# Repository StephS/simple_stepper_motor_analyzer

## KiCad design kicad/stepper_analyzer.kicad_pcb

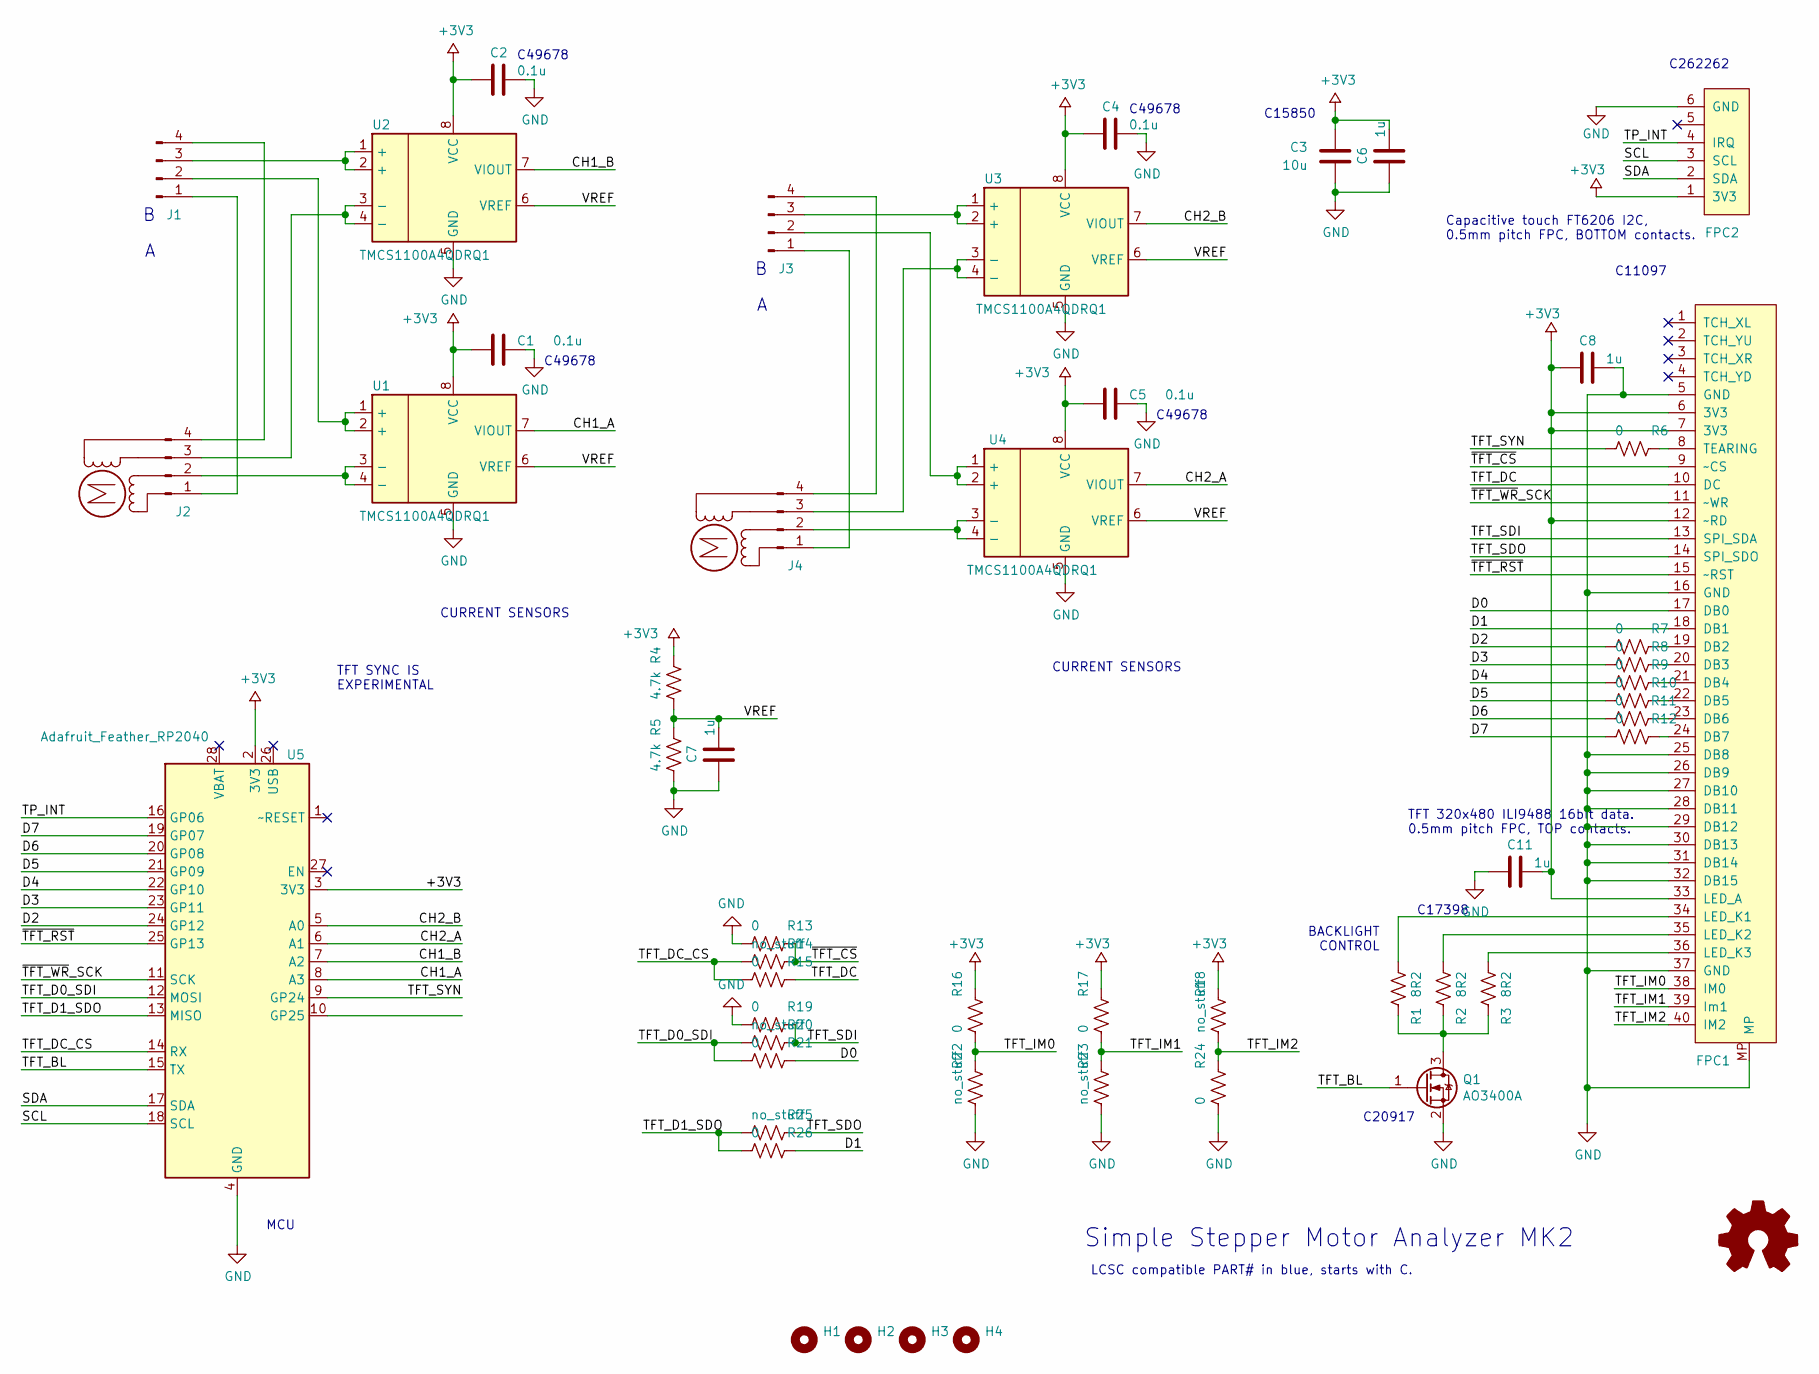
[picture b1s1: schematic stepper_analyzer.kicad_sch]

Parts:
C1, C2, C4, C5: 0.1u; C_0805_2012Metric_Pad1.15x1.40mm_HandSolder; LCSC C49678
C3: 10u; C_0805_2012Metric_Pad1.15x1.40mm_HandSolder; LCSC C15850
C6, C7, C8, C11: 1u; C_0805_2012Metric_Pad1.15x1.40mm_HandSolder
FPC1: Connector_Conn_01x40_Female; JUSHUO-AFC07-S40ECC-00_40P_05mm_flipped; LCSC C11097
FPC2: FPC connector, 6 pins, 0.5mm, BOTTOM contacts; JUSHUO-AFC01-S06FCC-00_6p_05mm; LCSC C262262
H1, H2, H3, H4: MountingHole; MountingHole_2.5mm_Pad_Via
J1, J2, J3, J4: Connector_Conn_01x04_Male; connector_4pins_horizontal
LOGO1: Logo_Open_Hardware_Small; OSHW-Logo2_9.8x8mm_SilkScreen
M1, M2: Motor; null_footprint
Q1: AO3400A; SOT-23; LCSC C20917
R1, R2, R3: 8R2; R_0805_2012Metric_Pad1.15x1.40mm_HandSolder; LCSC C25330
R4, R5: 4.7k; R_0402_1005Metric_Pad0.72x0.64mm_HandSolder
R6, R7, R8, R9, R10, R11, R12, R13, R15, R16, R17, R19, R21, R24, R26: 0; R_0402_1005Metric_Pad0.72x0.64mm_HandSolder
R14, R18, R20, R22, R23, R25: no_stuff; R_0402_1005Metric_Pad0.72x0.64mm_HandSolder
U1, U2, U3, U4: TMCS1100A4QDRQ1; SOIC-8_3.9x4.9mm_P1.27mm
U5: Adafruit_Feather_RP2040; Adafruit_Feather

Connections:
+3V3: C1.2, C2.2, C3.2, C4.2, C5.2, C6.1, C8.2, C11.1, FPC1.6 (3V3), FPC1.7 (3V3), FPC1.12 (~RD), FPC1.33 (LED_A), FPC2.1 (3V3), R4.1, R16.1, R17.1, R18.1, U1.8 (VCC), U2.8 (VCC), U3.8 (VCC), U4.8 (VCC), U5.2 (3V3), U5.3 (3V3)
/CH1_A: U1.7 (VIOUT), U5.8 (A3)
/CH1_B: U2.7 (VIOUT), U5.7 (A2)
/CH2_A: U4.7 (VIOUT), U5.6 (A1)
/CH2_B: U3.7 (VIOUT), U5.5 (A0)
/D0: FPC1.17 (DB0), R21.1
/D1: FPC1.18 (DB1), R26.1
/D2: R7.2, U5.24 (GP12)
/D3: R8.2, U5.23 (GP11)
/D4: R9.2, U5.22 (GP10)
/D5: R10.2, U5.21 (GP09)
/D6: R11.2, U5.20 (GP08)
/D7: R12.2, U5.19 (GP07)
/SCL: FPC2.3 (SCL), U5.18 (SCL)
/SDA: FPC2.2 (SDA), U5.17 (SDA)
/TFT_BL: Q1.1 (G), U5.15 (TX)
/TFT_D0_SDI: R20.2, R21.2, U5.12 (MOSI)
/TFT_D1_SDO: R25.2, R26.2, U5.13 (MISO)
/TFT_DC: FPC1.10 (DC), R15.1
/TFT_DC_CS: R14.2, R15.2, U5.14 (RX)
/TFT_IM0: FPC1.38 (IM0), R16.2, R22.1
/TFT_IM1: FPC1.39 (Im1), R17.2, R23.1
/TFT_IM2: FPC1.40 (IM2), R18.2, R24.1
/TFT_SDI: FPC1.13 (SPI_SDA), R19.1, R20.1
/TFT_SDO: FPC1.14 (SPI_SDO), R25.1
/TFT_SYN: R6.2, U5.9 (GP24)
/TP_INT: FPC2.4 (IRQ), U5.16 (GP06)
/VREF: C7.1, R4.2, R5.1, U1.6 (VREF), U2.6 (VREF), U3.6 (VREF), U4.6 (VREF)
/~TFT_CS: FPC1.9 (~CS), R13.1, R14.1
/~TFT_RST: FPC1.15 (~RST), U5.25 (GP13)
/~TFT_WR_SCK: FPC1.11 (~WR), U5.11 (SCK)
GND: C1.1, C2.1, C3.1, C4.1, C5.1, C6.2, C7.2, C8.1, C11.2, FPC1.5 (GND), FPC1.16 (GND), FPC1.25 (DB8), FPC1.26 (DB9), FPC1.27 (DB10), FPC1.28 (DB11), FPC1.29 (DB12), FPC1.30 (DB13), FPC1.31 (DB14), FPC1.32 (DB15), FPC1.37 (GND), FPC1.MP, FPC2.6 (GND), Q1.2 (S), R5.2, R13.2, R19.2, R22.2, R23.2, R24.2, U1.5 (GND), U2.5 (GND), U3.5 (GND), U4.5 (GND), U5.4 (GND)
unnamed: FPC1.8 (TEARING), R6.1
unnamed: FPC1.19 (DB2), R7.1
unnamed: FPC1.20 (DB3), R8.1
unnamed: FPC1.21 (DB4), R9.1
unnamed: FPC1.22 (DB5), R10.1
unnamed: FPC1.23 (DB6), R11.1
unnamed: FPC1.24 (DB7), R12.1
unnamed: FPC1.34 (LED_K1), R1.2
unnamed: FPC1.35 (LED_K2), R2.2
unnamed: FPC1.36 (LED_K3), R3.2
unnamed: J1.1, J2.1
unnamed: J1.2, U1.1 (+), U1.2 (+)
unnamed: J1.3, U2.1 (+), U2.2 (+)
unnamed: J1.4, J2.4
unnamed: J2.2, U1.3 (-), U1.4 (-)
unnamed: J2.3, U2.3 (-), U2.4 (-)
unnamed: J3.1, J4.1
unnamed: J3.2, U4.1 (+), U4.2 (+)
unnamed: J3.3, U3.1 (+), U3.2 (+)
unnamed: J3.4, J4.4
unnamed: J4.2, U4.3 (-), U4.4 (-)
unnamed: J4.3, U3.3 (-), U3.4 (-)
unnamed: Q1.3 (D), R1.1, R2.1, R3.1

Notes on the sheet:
MCU
TFT SYNC IS EXPERIMENTAL
C49678
CURRENT SENSORS
Simple Stepper Motor Analyzer MK2
LCSC compatible PART# in blue, starts with C.
C15850
C20917
BACKLIGHT CONTROL
TFT 320x480 ILI9488 16bit data. 0.5mm pitch FPC, TOP contacts.
C17398
Capacitive touch FT6206 I2C, 0.5mm pitch FPC, BOTTOM contacts.
C11097
C262262

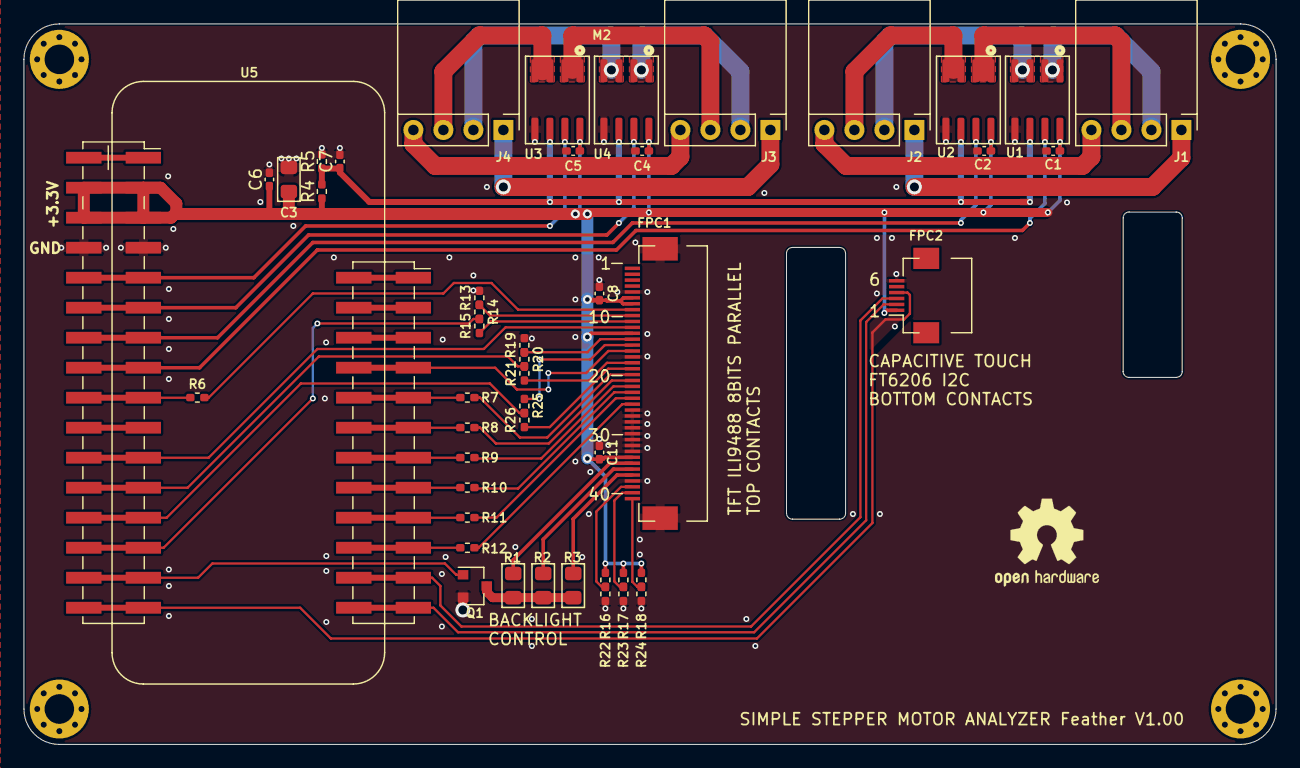
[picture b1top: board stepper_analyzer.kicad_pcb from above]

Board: 2 copper layers, 106.0 x 61.0 mm, 54 parts (0 on the bottom side), 55 nets.

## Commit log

2021-08-08 First version, v1.0 of feather
    2 stepper motor support using the ACS70311 sensors
2021-08-08 Update PCB to use TMCS1100A4QDRQ1
    TMCS1100A4QDRQ1 is compatible with the old current sense device, except needs a reference voltage.
2021-08-16 minor changes
